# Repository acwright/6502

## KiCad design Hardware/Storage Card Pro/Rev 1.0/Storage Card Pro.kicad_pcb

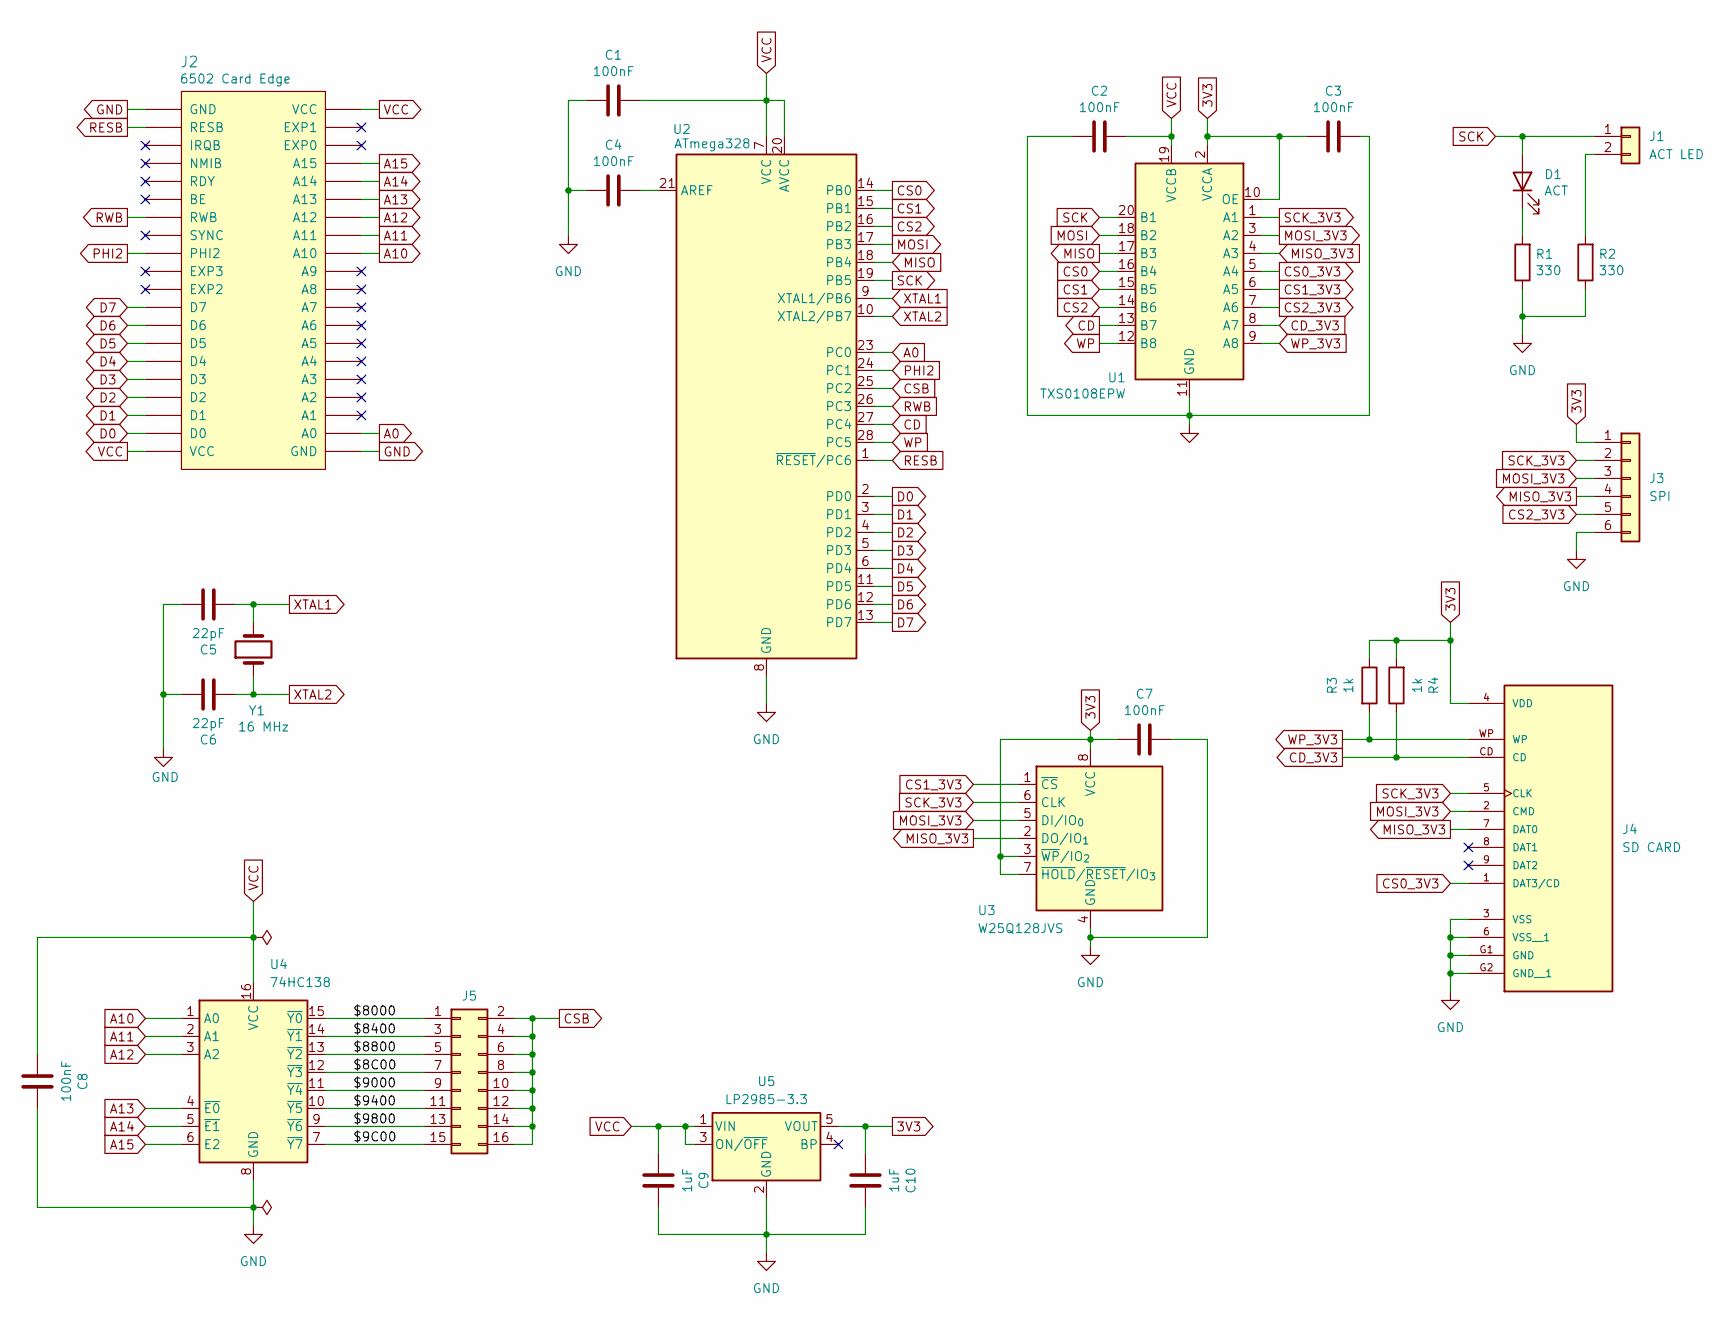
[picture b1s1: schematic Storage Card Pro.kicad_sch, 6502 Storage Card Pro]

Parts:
C1, C2, C3, C7, C8: 100nF; C_0805_2012Metric; LCSC C49678
C4: 100nF; C_0805_2012Metric
C5, C6: 22pF; C_Disc_D5.0mm_W2.5mm_P2.50mm; LCSC C107114
C9, C10: 1uF; C_0805_2012Metric; LCSC C28323
D1: ACT; LED_0805_2012Metric; LCSC C2297
J1: ACT LED; JST_XH_B2B-XH-A_1x02_P2.50mm_Vertical
J2: 6502 Card Edge
J3: SPI; PinHeader_1x06_P2.54mm_Horizontal
J4: SD CARD; 10067847-001RLF; PARTREV K; LCSC C569097
J5: Conn_02x08_Odd_Even; PinHeader_2x08_P2.54mm_Vertical
R1, R2: 330; R_0805_2012Metric; LCSC C17630
R3, R4: 1k; R_0805_2012Metric; LCSC C17513
U1: TXS0108EPW; TSSOP-20_4.4x6.5mm_P0.65mm; LCSC C17206
U2: ATmega328; DIP-28_W7.62mm_Socket_LongPads
U3: W25Q128JVS; SOIC-8_5.3x5.3mm_P1.27mm; LCSC C97521
U4: 74HC138; SOIC-16_3.9x9.9mm_P1.27mm; LCSC C5602
U5: LP2985-3.3; SOT-23-5; LCSC C95414
Y1: 16 MHz; Crystal_HC49-U_Vertical; Digikey 3155-16M20P2/49US-ND

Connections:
3V3: C3.1, C7.1, C10.1, J3.1, J4.4 (VDD), R3.1, R4.2, U1.2 (VCCA), U1.10 (OE), U3.3 (~WP/IO_{2}), U3.7 (~HOLD/~RESET/IO_{3}), U3.8 (VCC), U5.5 (VOUT)
/$8C00: J5.7, U4.12 (~Y3)
/$9C00: J5.15, U4.7 (~Y7)
/$8000: J5.1, U4.15 (~Y0)
/$8400: J5.3, U4.14 (~Y1)
/$8800: J5.5, U4.13 (~Y2)
/$9000: J5.9, U4.11 (~Y4)
/$9400: J5.11, U4.10 (~Y5)
/$9800: J5.13, U4.9 (~Y6)
A0: J2.A0, U2.23 (PC0)
A10: J2.A10, U4.1 (A0)
A11: J2.A11, U4.2 (A1)
A12: J2.A12, U4.3 (A2)
A13: J2.A13, U4.4 (~E0)
A14: J2.A14, U4.5 (~E1)
A15: J2.A15, U4.6 (E2)
CD: U1.13 (B7), U2.27 (PC4)
CD_3V3: J4.CD, R4.1, U1.8 (A7)
CS0: U1.16 (B4), U2.14 (PB0)
CS0_3V3: J4.1 (DAT3/CD), U1.5 (A4)
CS1: U1.15 (B5), U2.15 (PB1)
CS1_3V3: U1.6 (A5), U3.1 (~CS)
CS2: U1.14 (B6), U2.16 (PB2)
CS2_3V3: J3.5, U1.7 (A6)
CSB: J5.2, J5.4, J5.6, J5.8, J5.10, J5.12, J5.14, J5.16, U2.25 (PC2)
D0: J2.D0, U2.2 (PD0)
D1: J2.D1, U2.3 (PD1)
D2: J2.D2, U2.4 (PD2)
D3: J2.D3, U2.5 (PD3)
D4: J2.D4, U2.6 (PD4)
D5: J2.D5, U2.11 (PD5)
D6: J2.D6, U2.12 (PD6)
D7: J2.D7, U2.13 (PD7)
GND: C1.1, C2.1, C3.2, C4.1, C5.2, C6.2, C7.2, C8.2, C9.2, C10.2, J2.GND, J3.6, J4.3 (VSS), J4.6 (VSS__1), J4.G1 (GND), J4.G2 (GND__1), R1.1, R2.1, U1.11 (GND), U2.8 (GND), U2.22 (GND), U3.4 (GND), U4.8 (GND), U5.2 (GND)
MISO: U1.17 (B3), U2.18 (PB4)
MISO_3V3: J3.4, J4.7 (DAT0), U1.4 (A3), U3.2 (DO/IO_{1})
MOSI: U1.18 (B2), U2.17 (PB3)
MOSI_3V3: J3.3, J4.2 (CMD), U1.3 (A2), U3.5 (DI/IO_{0})
unnamed: D1.1 (K), R1.2
unnamed: J1.2, R2.2
unnamed: C4.2, U2.21 (AREF)
PHI2: J2.PHI2, U2.24 (PC1)
RESB: J2.RESB, U2.1 (~RESET/PC6)
RWB: J2.RWB, U2.26 (PC3)
SCK: D1.2 (A), J1.1, U1.20 (B1), U2.19 (PB5)
SCK_3V3: J3.2, J4.5 (CLK), U1.1 (A1), U3.6 (CLK)
VCC: C1.2, C2.2, C8.1, C9.1, J2.VCC, U1.19 (VCCB), U2.7 (VCC), U2.20 (AVCC), U4.16 (VCC), U5.1 (VIN), U5.3 (ON/~OFF)
WP: U1.12 (B8), U2.28 (PC5)
WP_3V3: J4.WP, R3.2, U1.9 (A8)
XTAL1: C5.1, U2.9 (XTAL1/PB6), Y1.2
XTAL2: C6.1, U2.10 (XTAL2/PB7), Y1.1

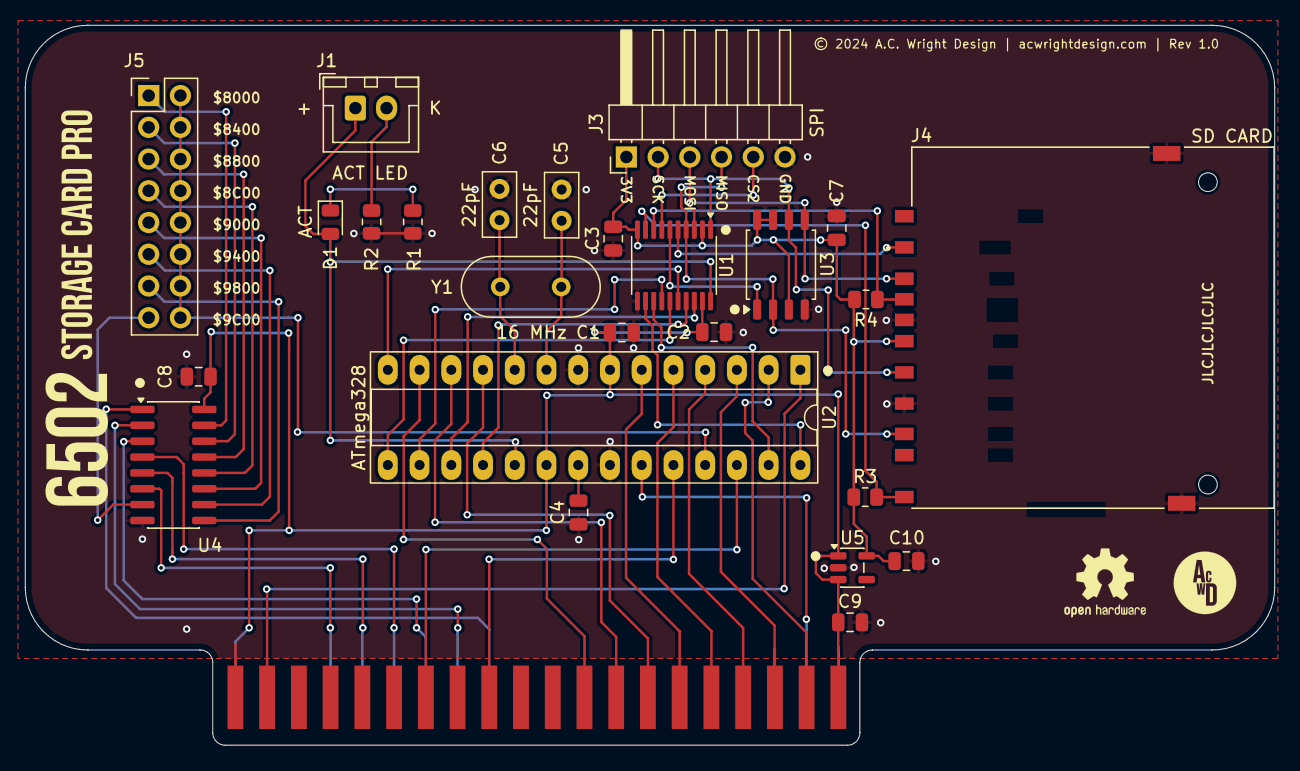
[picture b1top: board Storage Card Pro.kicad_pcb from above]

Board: 2 copper layers, 100.0 x 57.6 mm, 26 parts (0 on the bottom side), 51 nets.

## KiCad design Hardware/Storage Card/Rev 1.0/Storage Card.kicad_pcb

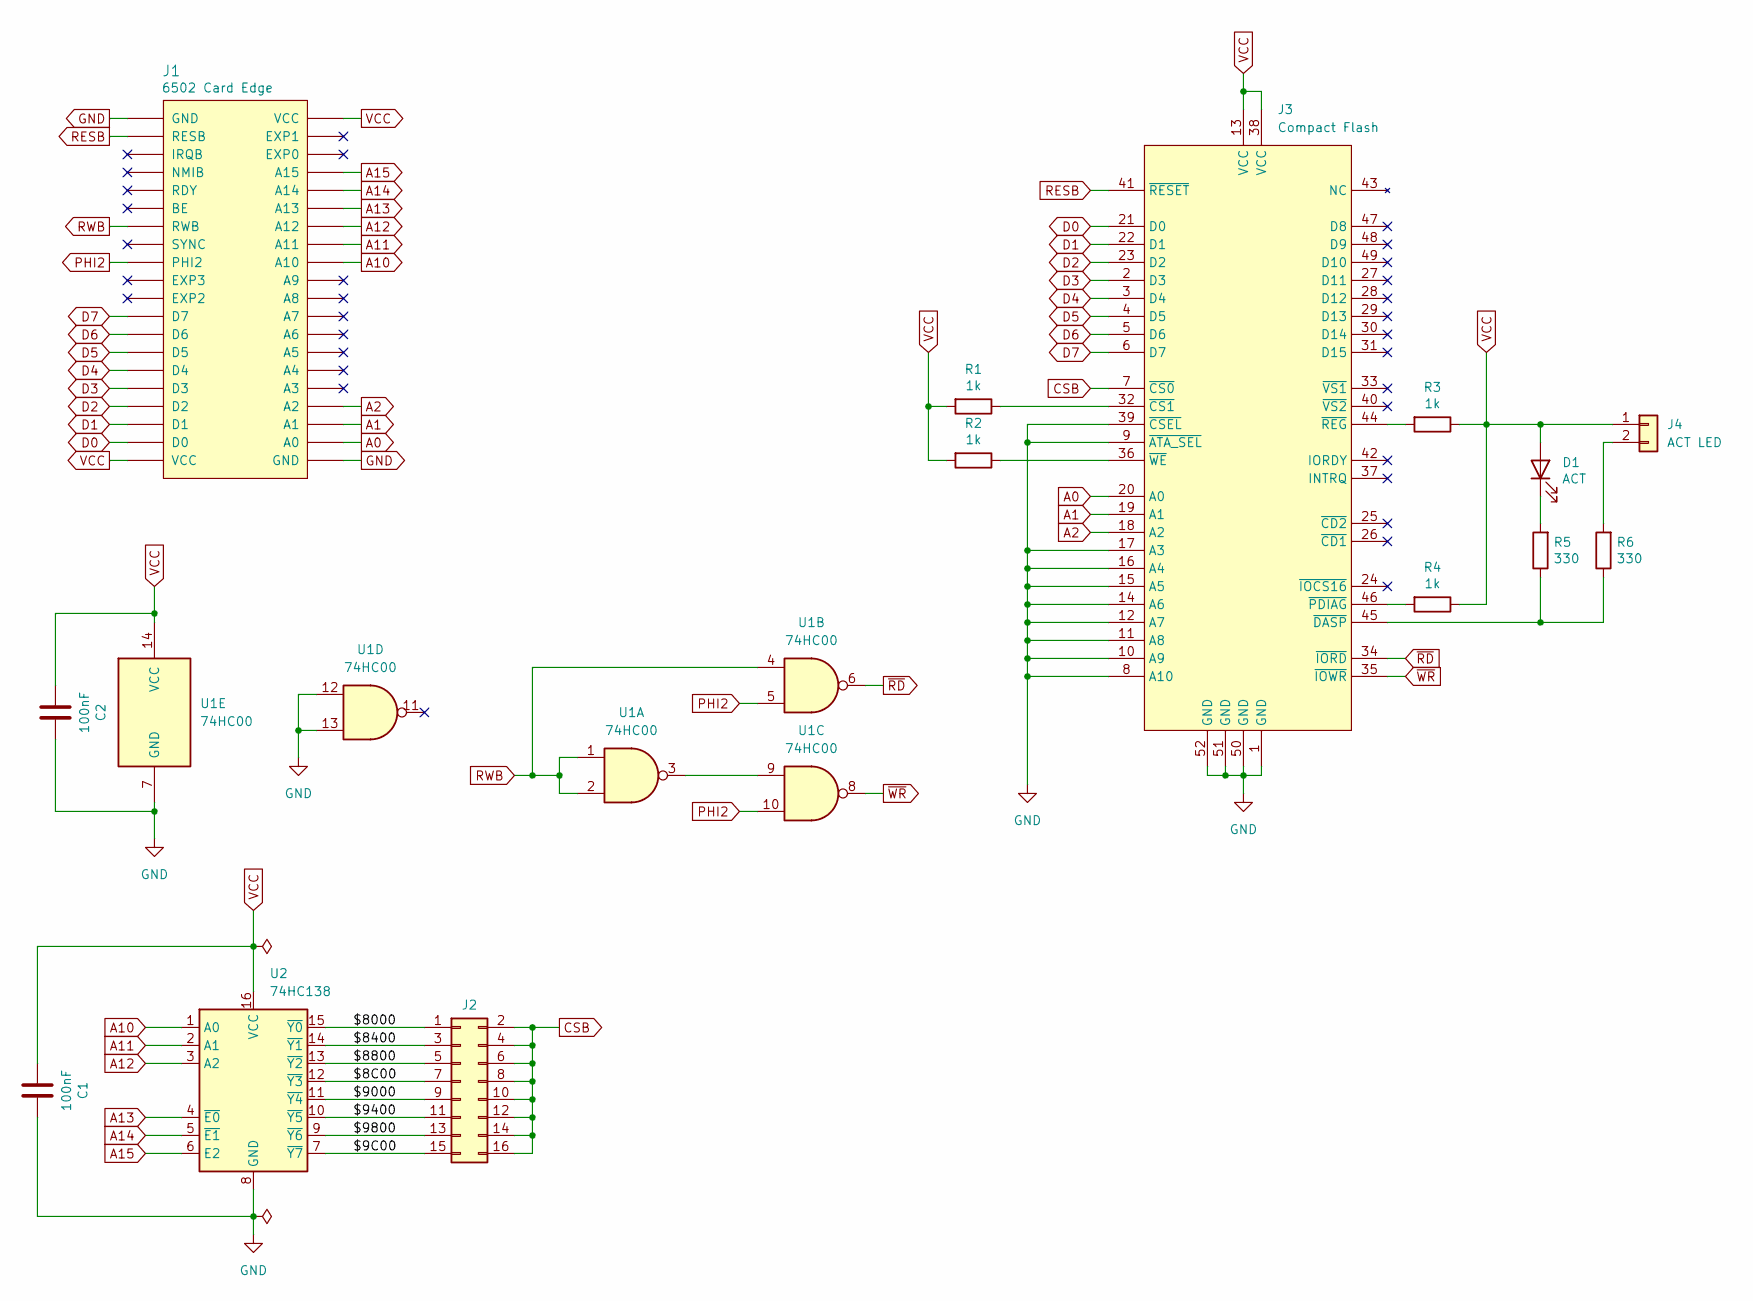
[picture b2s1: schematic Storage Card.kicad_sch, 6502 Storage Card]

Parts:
C1, C2: 100nF; C_0805_2012Metric; LCSC C49678
D1: ACT; LED_0805_2012Metric; LCSC C2297
J1: 6502 Card Edge
J2: Conn_02x08_Odd_Even; PinHeader_2x08_P2.54mm_Vertical
J3: Compact Flash; SD-SMD_CFH-L3C1LBL01MN0; LCSC C444350
J4: ACT LED; JST_XH_B2B-XH-A_1x02_P2.50mm_Vertical
R1, R2, R3, R4: 1k; R_0805_2012Metric; LCSC C17513
R5, R6: 330; R_0805_2012Metric; LCSC C17630
U1: 74HC00; SOIC-14_3.9x8.7mm_P1.27mm; LCSC C5586
U2: 74HC138; SOIC-16_3.9x9.9mm_P1.27mm; LCSC C5602

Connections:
/$8C00: J2.7, U2.12 (~Y3)
/$9C00: J2.15, U2.7 (~Y7)
/$8000: J2.1, U2.15 (~Y0)
/$8400: J2.3, U2.14 (~Y1)
/$8800: J2.5, U2.13 (~Y2)
/$9000: J2.9, U2.11 (~Y4)
/$9400: J2.11, U2.10 (~Y5)
/$9800: J2.13, U2.9 (~Y6)
A0: J1.A0, J3.20 (A0)
A1: J1.A1, J3.19 (A1)
A2: J1.A2, J3.18 (A2)
A10: J1.A10, U2.1 (A0)
A11: J1.A11, U2.2 (A1)
A12: J1.A12, U2.3 (A2)
A13: J1.A13, U2.4 (~E0)
A14: J1.A14, U2.5 (~E1)
A15: J1.A15, U2.6 (E2)
CSB: J2.2, J2.4, J2.6, J2.8, J2.10, J2.12, J2.14, J2.16, J3.7 (~CS0)
D0: J1.D0, J3.21 (D0)
D1: J1.D1, J3.22 (D1)
D2: J1.D2, J3.23 (D2)
D3: J1.D3, J3.2 (D3)
D4: J1.D4, J3.3 (D4)
D5: J1.D5, J3.4 (D5)
D6: J1.D6, J3.5 (D6)
D7: J1.D7, J3.6 (D7)
GND: C1.2, C2.2, J1.GND, J3.1 (GND), J3.8 (A10), J3.9 (~ATA_SEL), J3.10 (A9), J3.11 (A8), J3.12 (A7), J3.14 (A6), J3.15 (A5), J3.16 (A4), J3.17 (A3), J3.39 (~CSEL), J3.50 (GND), J3.51 (GND), J3.52 (GND), U1.7 (GND), U1.12, U1.13, U2.8 (GND)
unnamed: D1.1 (K), R5.2
unnamed: J3.32 (~CS1), R1.1
unnamed: J3.45 (~DASP), R5.1, R6.1
unnamed: J3.46 (~PDIAG), R4.2
unnamed: J3.44 (~REG), R3.2
unnamed: J3.36 (~WE), R2.1
unnamed: J4.2, R6.2
unnamed: U1.3, U1.9
PHI2: J1.PHI2, U1.5, U1.10
RESB: J1.RESB, J3.41 (~RESET)
RWB: J1.RWB, U1.1, U1.2, U1.4
VCC: C1.1, C2.1, D1.2 (A), J1.VCC, J3.13 (VCC), J3.38 (VCC), J4.1, R1.2, R2.2, R3.1, R4.1, U1.14 (VCC), U2.16 (VCC)
~RD: J3.34 (~IORD), U1.6
~WR: J3.35 (~IOWR), U1.8

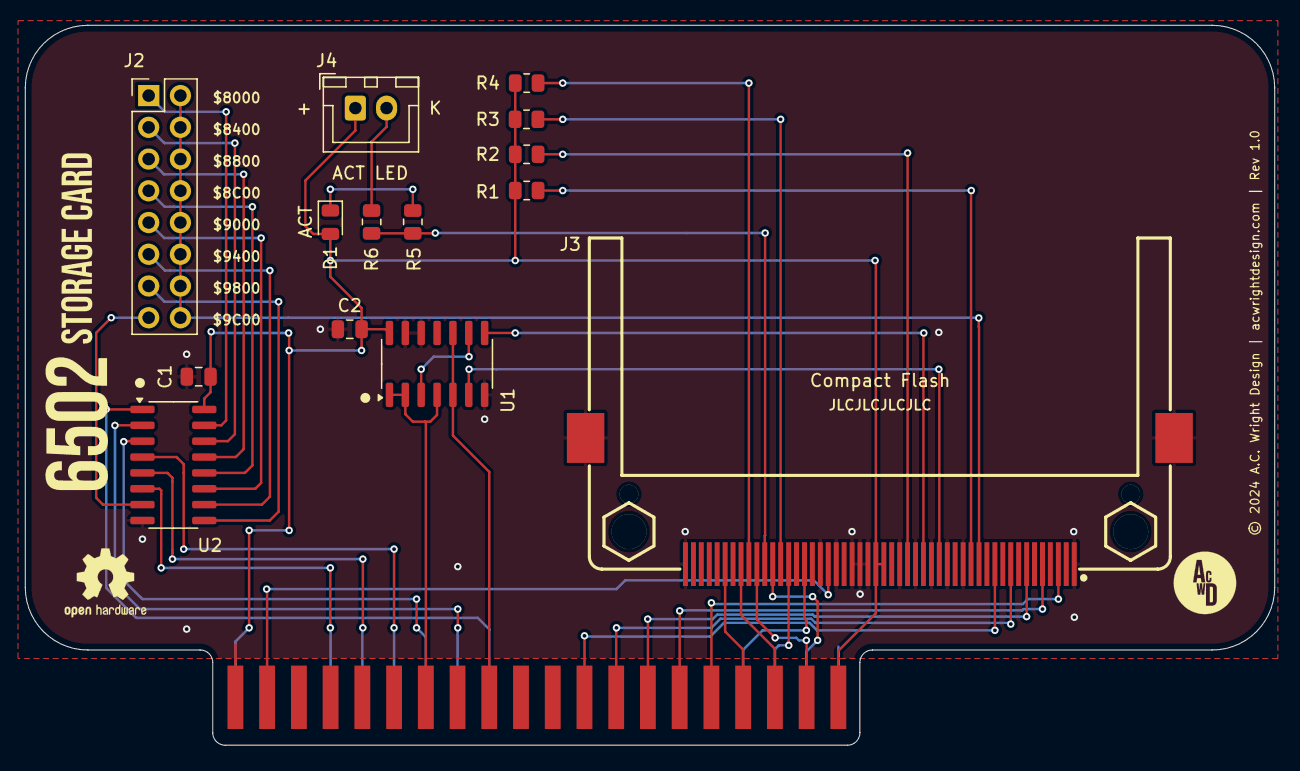
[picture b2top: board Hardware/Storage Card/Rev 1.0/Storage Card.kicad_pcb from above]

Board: 2 copper layers, 100.0 x 57.6 mm, 15 parts (0 on the bottom side), 41 nets.

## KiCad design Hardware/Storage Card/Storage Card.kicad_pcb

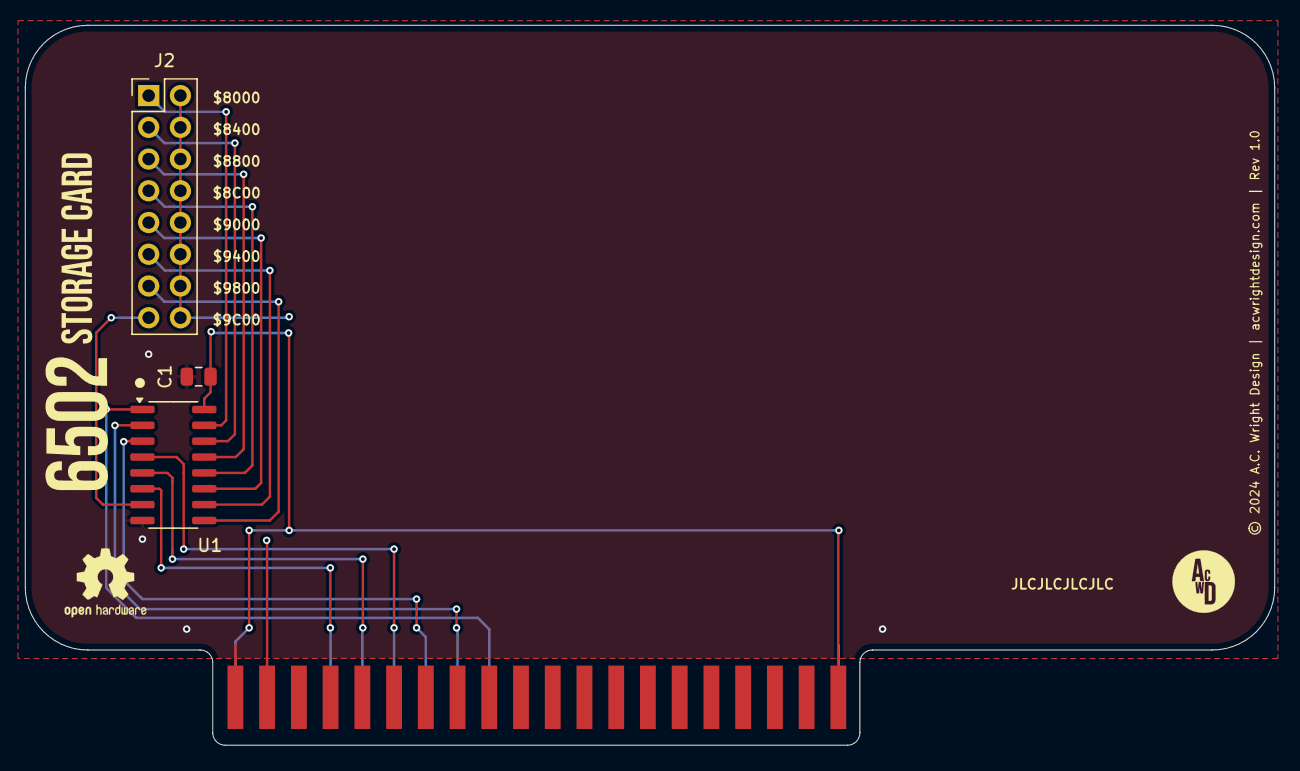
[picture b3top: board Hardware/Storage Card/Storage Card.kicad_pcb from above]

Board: 2 copper layers, 100.0 x 57.6 mm, 4 parts (0 on the bottom side), 17 nets.

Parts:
C1: 100nF; C_0805_2012Metric
J1: 6502 Card Edge
J2: Conn_02x08_Odd_Even; PinHeader_2x08_P2.54mm_Vertical
U1: 74HC138; SOIC-16_3.9x9.9mm_P1.27mm

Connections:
/$8C00: J2.7, U1.12 (~Y3)
/$9C00: J2.15, U1.7 (~Y7)
/$8000: J2.1, U1.15 (~Y0)
/$8400: J2.3, U1.14 (~Y1)
/$8800: J2.5, U1.13 (~Y2)
/$9000: J2.9, U1.11 (~Y4)
/$9400: J2.11, U1.10 (~Y5)
/$9800: J2.13, U1.9 (~Y6)
A10: J1.A10, U1.1 (A0)
A11: J1.A11, U1.2 (A1)
A12: J1.A12, U1.3 (A2)
A13: J1.A13, U1.4 (~E0)
A14: J1.A14, U1.5 (~E1)
A15: J1.A15, U1.6 (E2)
CSB: J2.2, J2.4, J2.6, J2.8, J2.10, J2.12, J2.14, J2.16
GND: C1.2, J1.GND, U1.8 (GND)
VCC: C1.1, J1.VCC, U1.16 (VCC)

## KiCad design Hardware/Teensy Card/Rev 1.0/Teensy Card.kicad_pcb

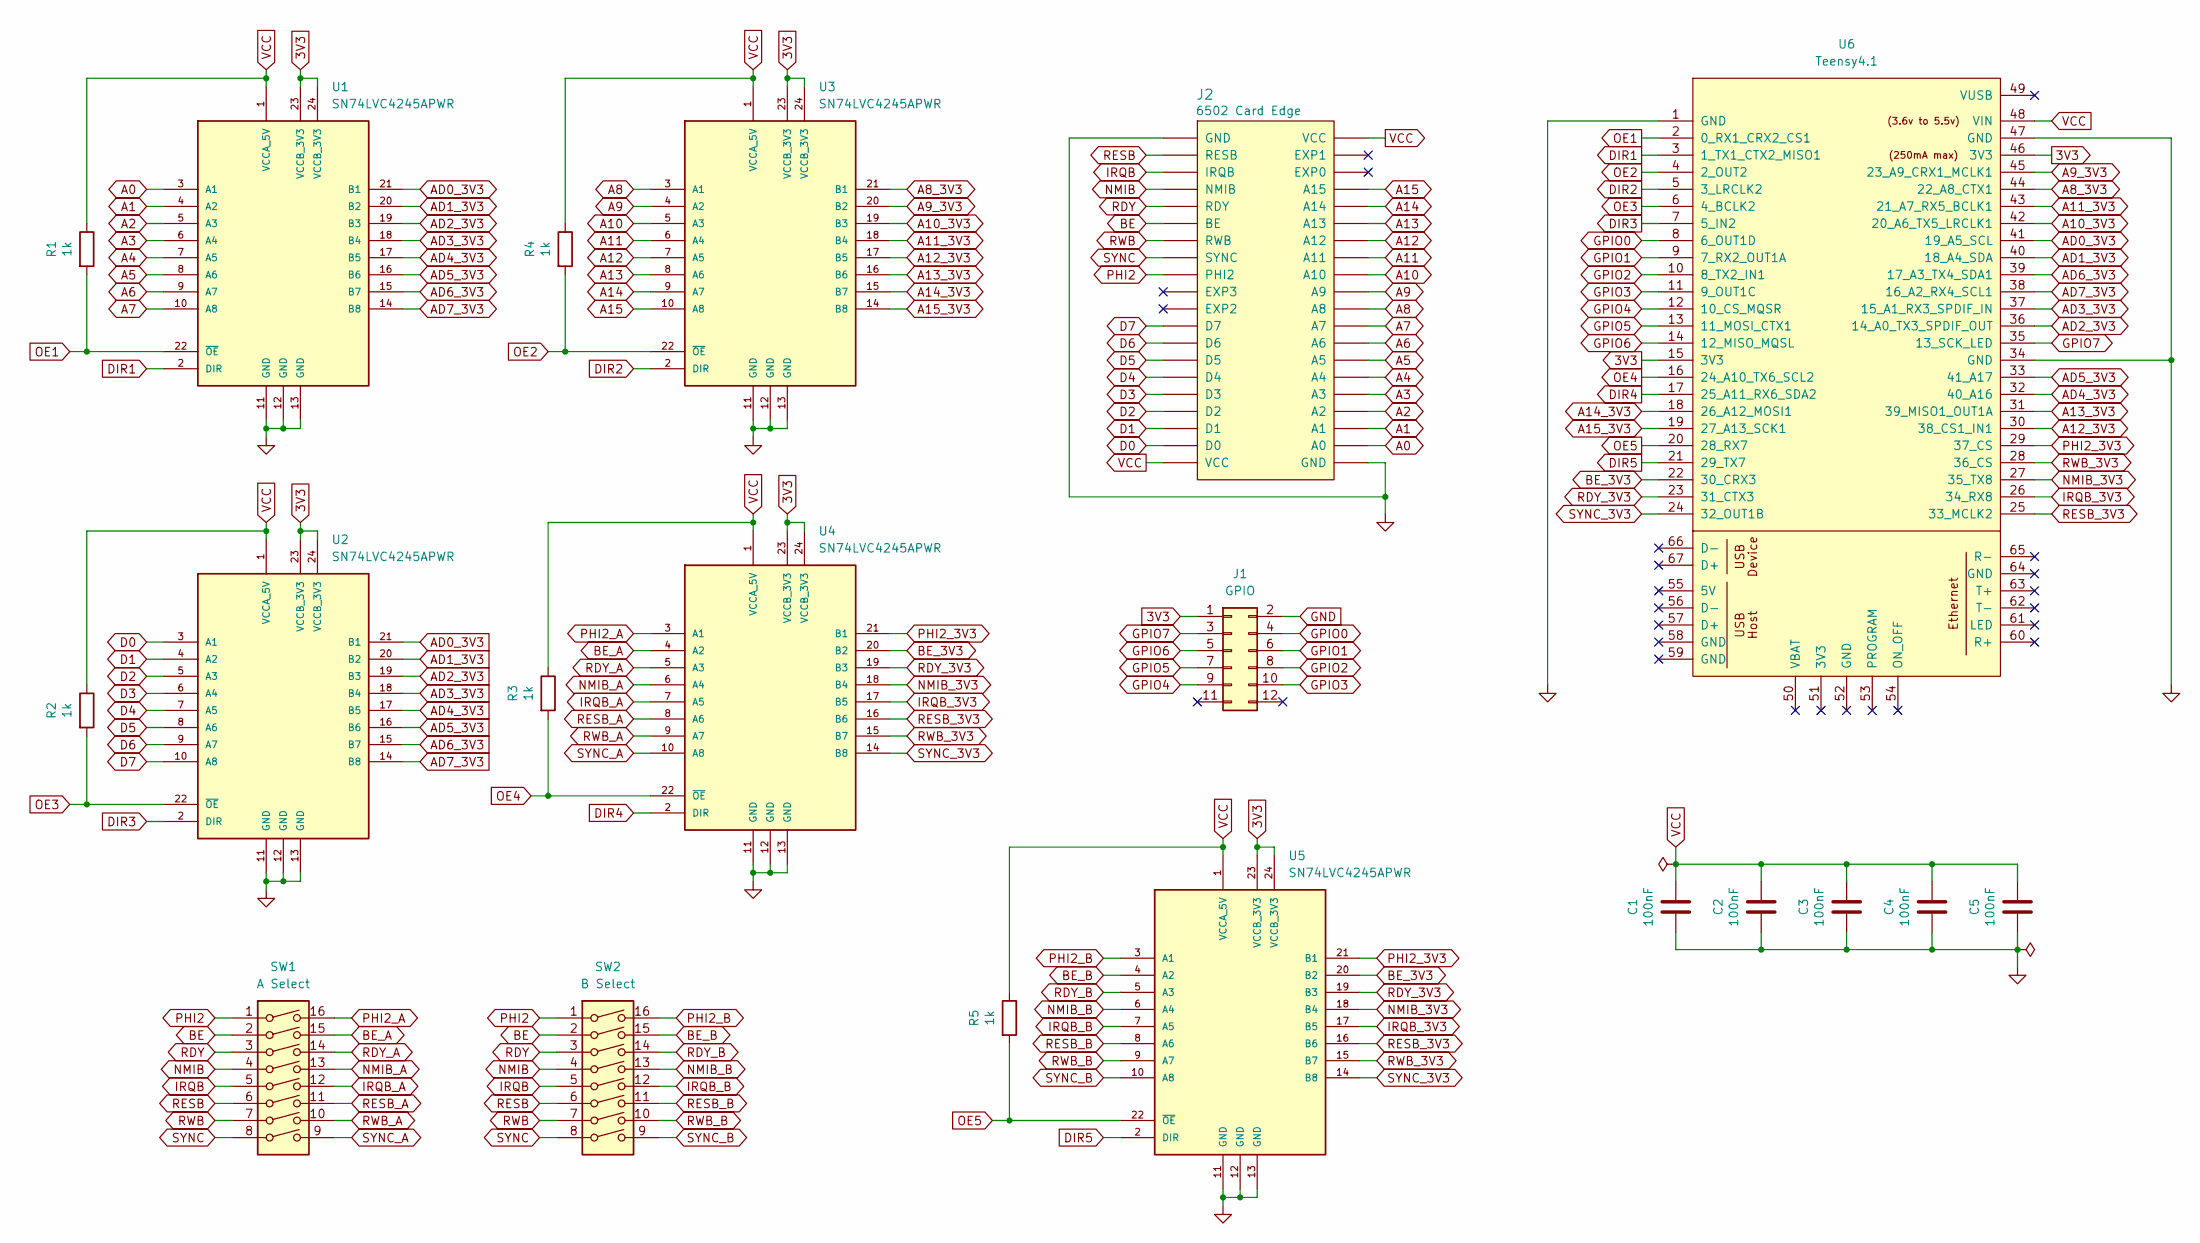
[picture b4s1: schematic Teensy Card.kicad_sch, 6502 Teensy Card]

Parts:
C1, C2, C3, C4, C5: 100nF; C_0805_2012Metric; LCSC C49678
J1: GPIO; 6502 GPIO Connector
J2: 6502 Card Edge
R1, R2, R3, R4, R5: 1k; R_0805_2012Metric; LCSC C17513
SW1: A Select; DS01C-254-L-08BE
SW2: B Select; DS01C-254-L-08BE
U1, U2, U3, U4, U5: SN74LVC4245APWR; TSSOP-24_4.4x7.8mm_P0.65mm; LCSC C7859
U6: Teensy4.1; Teensy41 Basic

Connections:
3V3: J1.1, U1.23 (VCCB_3V3), U1.24 (VCCB_3V3), U2.23 (VCCB_3V3), U2.24 (VCCB_3V3), U3.23 (VCCB_3V3), U3.24 (VCCB_3V3), U4.23 (VCCB_3V3), U4.24 (VCCB_3V3), U5.23 (VCCB_3V3), U5.24 (VCCB_3V3), U6.15 (3V3), U6.46 (3V3)
A0: J2.A0, U1.3 (A1)
A1: J2.A1, U1.4 (A2)
A2: J2.A2, U1.5 (A3)
A3: J2.A3, U1.6 (A4)
A4: J2.A4, U1.7 (A5)
A5: J2.A5, U1.8 (A6)
A6: J2.A6, U1.9 (A7)
A7: J2.A7, U1.10 (A8)
A8: J2.A8, U3.3 (A1)
A8_3V3: U3.21 (B1), U6.44 (22_A8_CTX1)
A9: J2.A9, U3.4 (A2)
A9_3V3: U3.20 (B2), U6.45 (23_A9_CRX1_MCLK1)
A10: J2.A10, U3.5 (A3)
A10_3V3: U3.19 (B3), U6.42 (20_A6_TX5_LRCLK1)
A11: J2.A11, U3.6 (A4)
A11_3V3: U3.18 (B4), U6.43 (21_A7_RX5_BCLK1)
A12: J2.A12, U3.7 (A5)
A12_3V3: U3.17 (B5), U6.30 (38_CS1_IN1)
A13: J2.A13, U3.8 (A6)
A13_3V3: U3.16 (B6), U6.31 (39_MISO1_OUT1A)
A14: J2.A14, U3.9 (A7)
A14_3V3: U3.15 (B7), U6.18 (26_A12_MOSI1)
A15: J2.A15, U3.10 (A8)
A15_3V3: U3.14 (B8), U6.19 (27_A13_SCK1)
AD0_3V3: U1.21 (B1), U2.21 (B1), U6.41 (19_A5_SCL)
AD1_3V3: U1.20 (B2), U2.20 (B2), U6.40 (18_A4_SDA)
AD2_3V3: U1.19 (B3), U2.19 (B3), U6.36 (14_A0_TX3_SPDIF_OUT)
AD3_3V3: U1.18 (B4), U2.18 (B4), U6.37 (15_A1_RX3_SPDIF_IN)
AD4_3V3: U1.17 (B5), U2.17 (B5), U6.32 (40_A16)
AD5_3V3: U1.16 (B6), U2.16 (B6), U6.33 (41_A17)
AD6_3V3: U1.15 (B7), U2.15 (B7), U6.39 (17_A3_TX4_SDA1)
AD7_3V3: U1.14 (B8), U2.14 (B8), U6.38 (16_A2_RX4_SCL1)
BE: J2.BE, SW1.2, SW2.2
BE_3V3: U4.20 (B2), U5.20 (B2), U6.22 (30_CRX3)
BE_A: SW1.15, U4.4 (A2)
BE_B: SW2.15, U5.4 (A2)
D0: J2.D0, U2.3 (A1)
D1: J2.D1, U2.4 (A2)
D2: J2.D2, U2.5 (A3)
D3: J2.D3, U2.6 (A4)
D4: J2.D4, U2.7 (A5)
D5: J2.D5, U2.8 (A6)
D6: J2.D6, U2.9 (A7)
D7: J2.D7, U2.10 (A8)
DIR1: U1.2 (DIR), U6.3 (1_TX1_CTX2_MISO1)
DIR2: U3.2 (DIR), U6.5 (3_LRCLK2)
DIR3: U2.2 (DIR), U6.7 (5_IN2)
DIR4: U4.2 (DIR), U6.17 (25_A11_RX6_SDA2)
DIR5: U5.2 (DIR), U6.21 (29_TX7)
GND: C1.2, C2.2, C3.2, C4.2, C5.2, J1.2, J2.GND, U1.11 (GND), U1.12 (GND), U1.13 (GND), U2.11 (GND), U2.12 (GND), U2.13 (GND), U3.11 (GND), U3.12 (GND), U3.13 (GND), U4.11 (GND), U4.12 (GND), U4.13 (GND), U5.11 (GND), U5.12 (GND), U5.13 (GND), U6.1 (GND), U6.34 (GND), U6.47 (GND)
GPIO0: J1.4, U6.8 (6_OUT1D)
GPIO1: J1.6, U6.9 (7_RX2_OUT1A)
GPIO2: J1.8, U6.10 (8_TX2_IN1)
GPIO3: J1.10, U6.11 (9_OUT1C)
GPIO4: J1.9, U6.12 (10_CS_MQSR)
GPIO5: J1.7, U6.13 (11_MOSI_CTX1)
GPIO6: J1.5, U6.14 (12_MISO_MQSL)
GPIO7: J1.3, U6.35 (13_SCK_LED)
IRQB: J2.IRQB, SW1.5, SW2.5
IRQB_3V3: U4.17 (B5), U5.17 (B5), U6.26 (34_RX8)
IRQB_A: SW1.12, U4.7 (A5)
IRQB_B: SW2.12, U5.7 (A5)
NMIB: J2.NMIB, SW1.4, SW2.4
NMIB_3V3: U4.18 (B4), U5.18 (B4), U6.27 (35_TX8)
NMIB_A: SW1.13, U4.6 (A4)
NMIB_B: SW2.13, U5.6 (A4)
OE1: R1.2, U1.22 (~OE), U6.2 (0_RX1_CRX2_CS1)
OE2: R4.2, U3.22 (~OE), U6.4 (2_OUT2)
OE3: R2.2, U2.22 (~OE), U6.6 (4_BCLK2)
OE4: R3.2, U4.22 (~OE), U6.16 (24_A10_TX6_SCL2)
OE5: R5.2, U5.22 (~OE), U6.20 (28_RX7)
PHI2: J2.PHI2, SW1.1, SW2.1
PHI2_3V3: U4.21 (B1), U5.21 (B1), U6.29 (37_CS)
PHI2_A: SW1.16, U4.3 (A1)
PHI2_B: SW2.16, U5.3 (A1)
RDY: J2.RDY, SW1.3, SW2.3
RDY_3V3: U4.19 (B3), U5.19 (B3), U6.23 (31_CTX3)
RDY_A: SW1.14, U4.5 (A3)
RDY_B: SW2.14, U5.5 (A3)
RESB: J2.RESB, SW1.6, SW2.6
RESB_3V3: U4.16 (B6), U5.16 (B6), U6.25 (33_MCLK2)
RESB_A: SW1.11, U4.8 (A6)
RESB_B: SW2.11, U5.8 (A6)
RWB: J2.RWB, SW1.7, SW2.7
RWB_3V3: U4.15 (B7), U5.15 (B7), U6.28 (36_CS)
RWB_A: SW1.10, U4.9 (A7)
RWB_B: SW2.10, U5.9 (A7)
SYNC: J2.SYNC, SW1.8, SW2.8
SYNC_3V3: U4.14 (B8), U5.14 (B8), U6.24 (32_OUT1B)
SYNC_A: SW1.9, U4.10 (A8)
SYNC_B: SW2.9, U5.10 (A8)
VCC: C1.1, C2.1, C3.1, C4.1, C5.1, J2.VCC, R1.1, R2.1, R3.1, R4.1, R5.1, U1.1 (VCCA_5V), U2.1 (VCCA_5V), U3.1 (VCCA_5V), U4.1 (VCCA_5V), U5.1 (VCCA_5V), U6.48 (VIN)

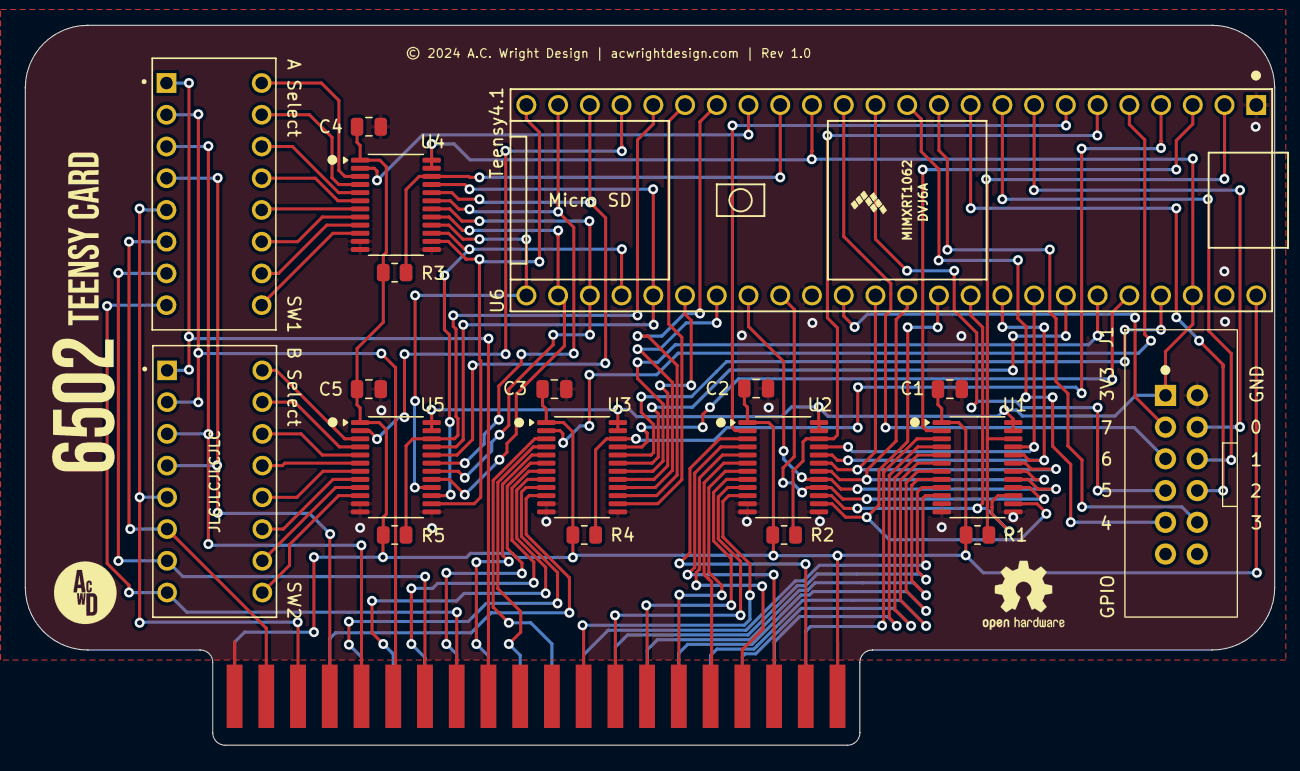
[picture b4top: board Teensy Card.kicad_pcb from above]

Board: 2 copper layers, 100.0 x 57.6 mm, 20 parts (0 on the bottom side), 93 nets.

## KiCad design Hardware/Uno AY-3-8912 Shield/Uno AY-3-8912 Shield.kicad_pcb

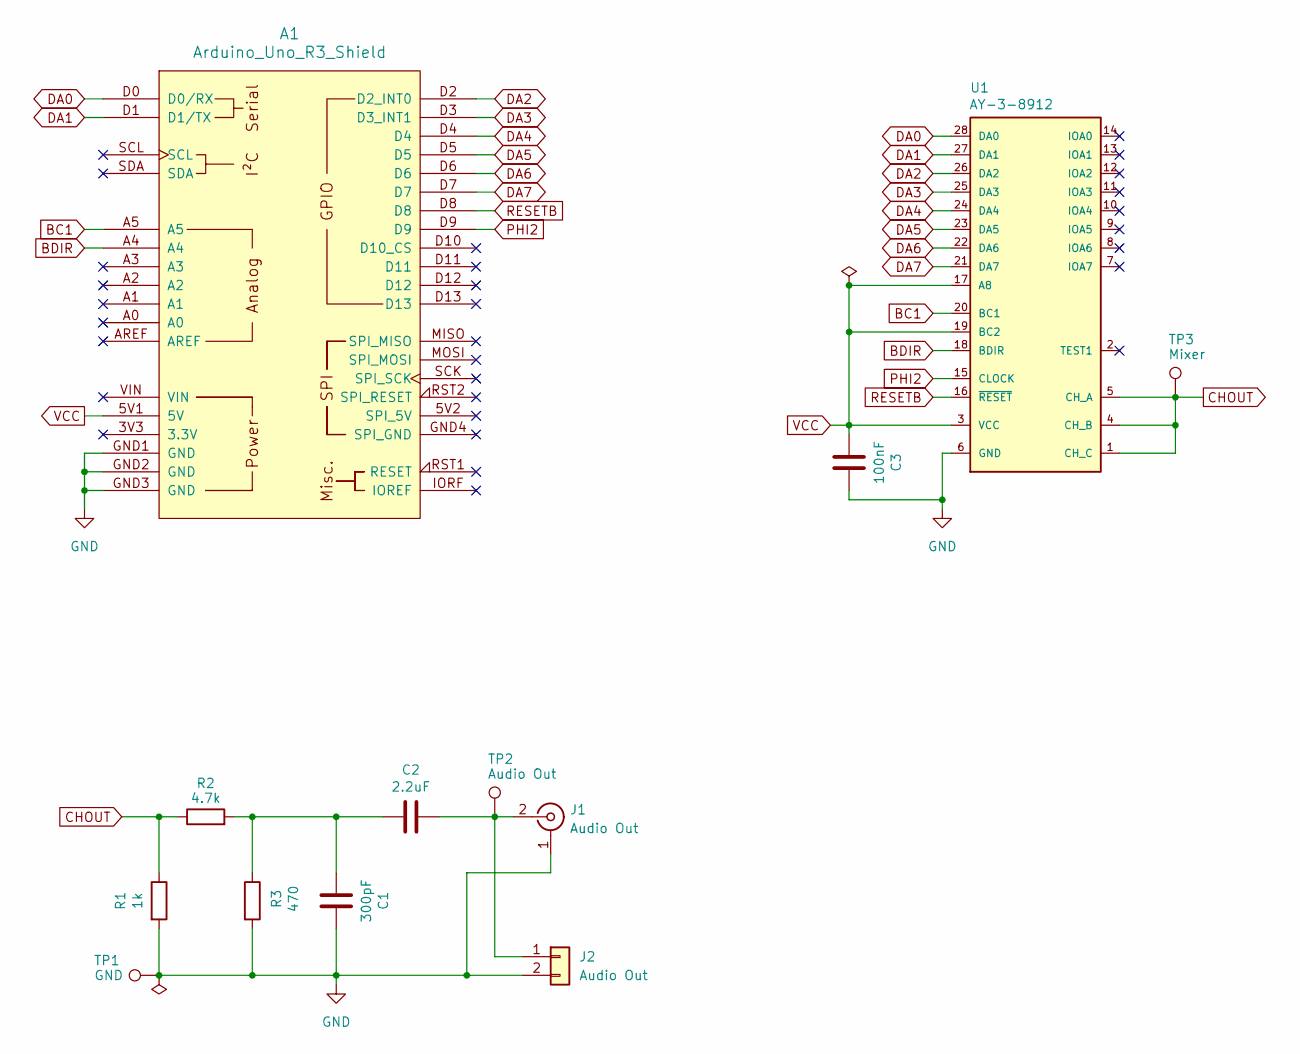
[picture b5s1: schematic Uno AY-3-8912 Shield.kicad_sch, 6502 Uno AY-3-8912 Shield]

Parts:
A1: Arduino_Uno_R3_Shield
C1: 300pF; C_Disc_D5.0mm_W2.5mm_P2.50mm; LCSC C37635
C2: 2.2uF; C_Disc_D5.0mm_W2.5mm_P2.50mm; LCSC C377773
C3: 100nF; C_Disc_D5.0mm_W2.5mm_P2.50mm; LCSC C49678
J1: Audio Out; SWITCHCRAFT_PJRAN1X1U02X
J2: Audio Out; JST_XH_B2B-XH-A_1x02_P2.50mm_Vertical
R1: 1k; R_Axial_DIN0309_L9.0mm_D3.2mm_P12.70mm_Horizontal; LCSC C17513
R2: 4.7k; R_Axial_DIN0309_L9.0mm_D3.2mm_P12.70mm_Horizontal; LCSC C17673
R3: 470; R_Axial_DIN0309_L9.0mm_D3.2mm_P12.70mm_Horizontal; LCSC C17710
TP1: GND; TestPoint_Pad_1.5x1.5mm
TP2: Audio Out; TestPoint_Pad_1.5x1.5mm
TP3: Mixer; TestPoint_Pad_1.5x1.5mm
U1: AY-3-8912; DIP_Socket-28_W11.9_W12.7_W15.24_W17.78_W18.5_3M_228-1277-0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

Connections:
BC1: A1.A5, U1.20 (BC1)
BDIR: A1.A4, U1.18 (BDIR)
CHOUT: R1.1, R2.1, TP3.1, U1.1 (CH_C), U1.4 (CH_B), U1.5 (CH_A)
DA0: A1.D0 (D0/RX), U1.28 (DA0)
DA1: A1.D1 (D1/TX), U1.27 (DA1)
DA2: A1.D2 (D2_INT0), U1.26 (DA2)
DA3: A1.D3 (D3_INT1), U1.25 (DA3)
DA4: A1.D4, U1.24 (DA4)
DA5: A1.D5, U1.23 (DA5)
DA6: A1.D6, U1.22 (DA6)
DA7: A1.D7, U1.21 (DA7)
GND: A1.GND1 (GND), A1.GND2 (GND), A1.GND3 (GND), C1.2, C3.2, J1.1 (Ext), J2.2, R1.2, R3.2, TP1.1, U1.6 (GND)
unnamed: C1.1, C2.1, R2.2, R3.1
unnamed: C2.2, J1.2 (In), J2.1, TP2.1
PHI2: A1.D9, U1.15 (CLOCK)
RESETB: A1.D8, U1.16 (~RESET)
VCC: A1.5V1 (5V), C3.1, U1.3 (VCC), U1.17 (A8), U1.19 (BC2)

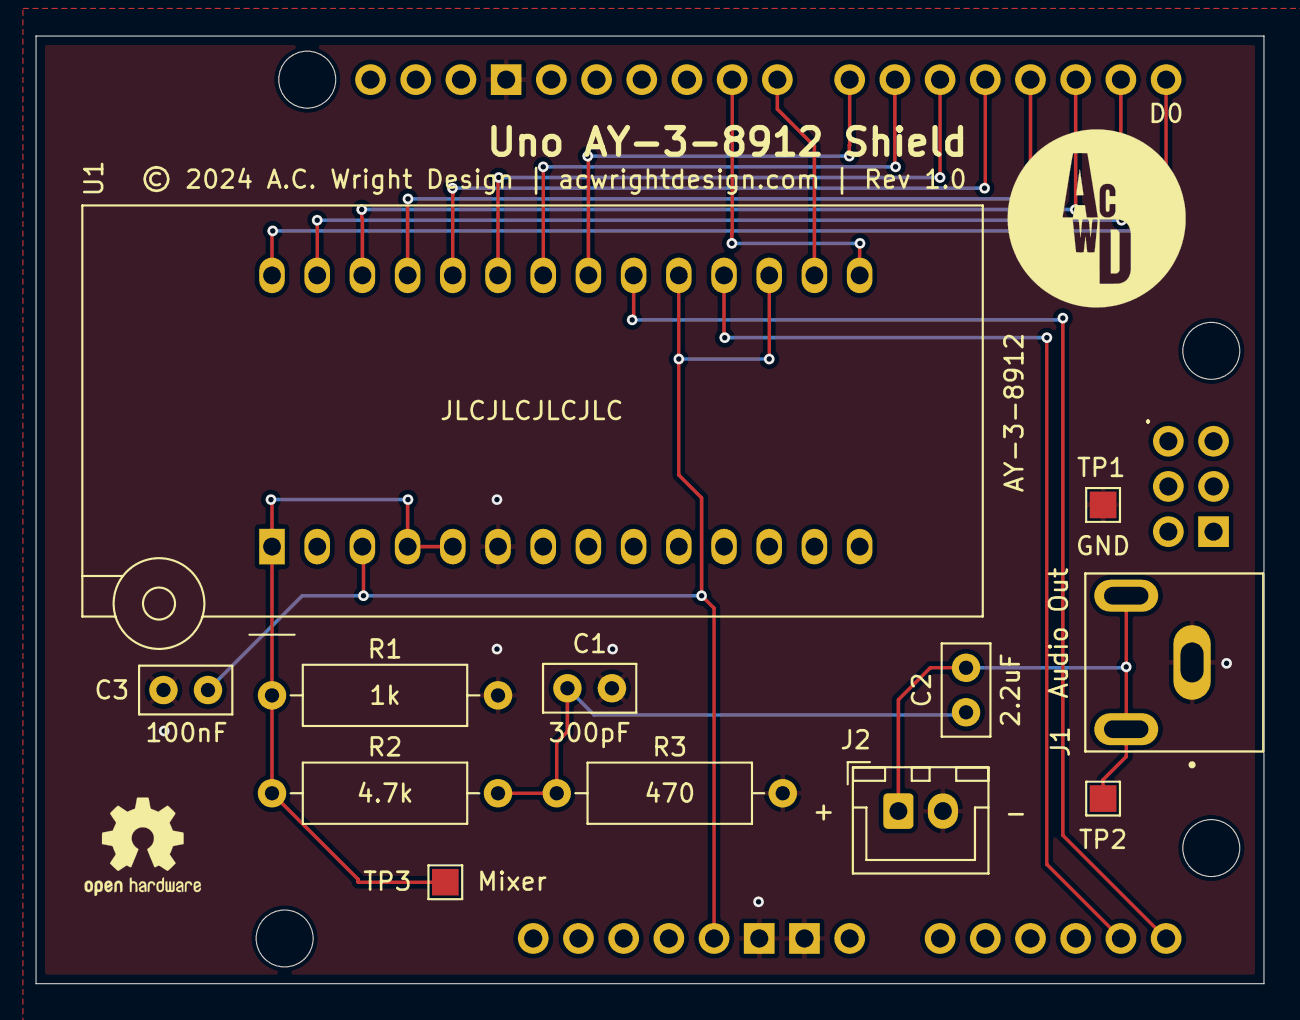
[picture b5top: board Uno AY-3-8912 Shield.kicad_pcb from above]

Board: 2 copper layers, 69.0 x 53.2 mm, 13 parts (0 on the bottom side), 17 nets.

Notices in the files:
Hardware/Storage Card Pro/Rev 1.0/Storage Card Pro.kicad_pcb:
© 2024 A.C. Wright Design | acwrightdesign.com | Rev 1.0
